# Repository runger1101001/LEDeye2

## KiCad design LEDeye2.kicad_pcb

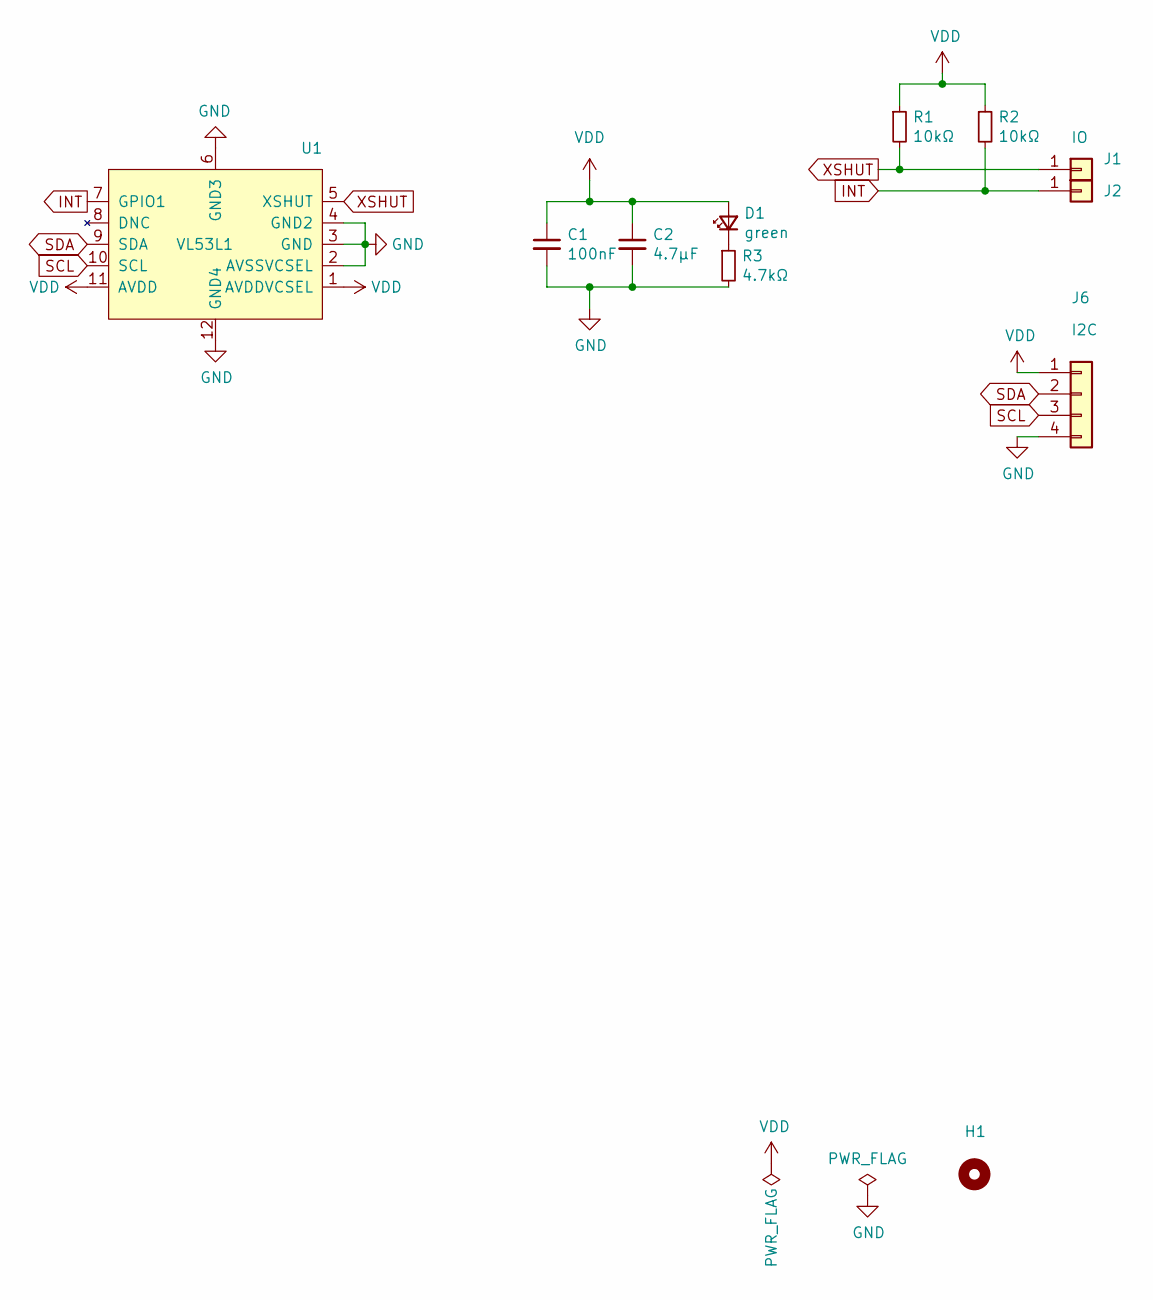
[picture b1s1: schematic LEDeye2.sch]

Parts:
C1: 100nF; C_0402_1005Metric
C2: 4.7µF; C_0402_1005Metric
D1: green; LED_0402_1005Metric
H1: MountingHole_Pad; MountingHole_2.2mm_M2_DIN965_Pad
J1, J2: IO; PinHeader_1x01_P1.27mm_Vertical
J6: I2C; JST_SH_BM04B-SRSS-TB_1x04-1MP_P1.00mm_Vertical; Part SM04B-SRSS-TB
R1, R2: 10kΩ; R_0402_1005Metric
R3: 4.7kΩ; R_0402_1005Metric
U1: VL53L1

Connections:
GND: C1.2, C2.2, J6.4, R3.2, U1.2 (AVSSVCSEL), U1.3 (GND), U1.4 (GND2), U1.6 (GND3), U1.12 (GND4)
INT: J2.1, R2.2, U1.7 (GPIO1)
unnamed: D1.1 (K), R3.1
SCL: J6.3, U1.10 (SCL)
SDA: J6.2, U1.9 (SDA)
VDD: C1.1, C2.1, D1.2 (A), J6.1, R1.1, R2.1, U1.1 (AVDDVCSEL), U1.11 (AVDD)
XSHUT: J1.1, R1.2, U1.5 (XSHUT)

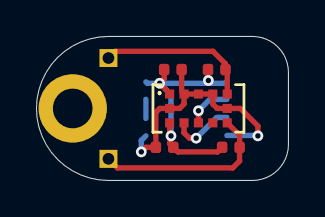
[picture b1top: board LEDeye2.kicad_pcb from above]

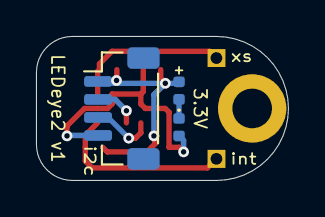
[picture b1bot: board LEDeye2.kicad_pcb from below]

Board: 2 copper layers, 14.0 x 8.0 mm, 11 parts (3 on the bottom side), 7 nets.

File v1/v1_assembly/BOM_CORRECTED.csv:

Item #,Ref Des,Qty,Manufacturer,Mfg Part #, Description / Value,Package,Type,Your Instructions / Notes
1,C1,1,Generic,Capacitor,100nF 6.3V,0402,SMD,"Unpolarized capacitor, small symbol"
2,C2,1,Generic,Capacitor,4.7µF 6.3V,0402,SMD,"Unpolarized capacitor, small symbol"
3,D1,1,Generic,SML-P12MTT86,LED Green (λ 560nm)  Vf 2.1V @20mA,0402,SMD,"Light emitting diode, small symbol"
4,"R1, R2",2,Generic,Resistor,10kΩ,0402,SMD,"Resistor, small symbol"
5,R3,1,Generic,Resistor,4.7kΩ,0402,SMD,"Resistor, small symbol"
6,U1,1,ST Micro,VL53L1,VL53L1,"Optical LGA12 
QFN_BV0FY1_STM",SMD,Time-of-Flight ranging sensor with advanced multi-zone and multi-object detection
7,J6,1,JST,BM04B-SRSS-TB ,BM04B-SRSS-TB  4-pin Vertical,BM04B-SRSS-TB ,SMD,JST SH 4-pin Vertical

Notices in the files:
parts and their libraries:
Copyright 2016 Accelerated Designs. All rights reserved.
